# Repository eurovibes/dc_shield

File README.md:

<!-- SPDX-FileCopyrightText: 2023 Benedikt Spranger <b.spranger@linutronix.de> -
->
<!-- SPDX-License-Identifier: CERN-OHL-S-2.0 -->

# dc_shield - A IFX9201 based Arduino Uno R3 motor shield

## License rules

dc_shield is provided under the terms of the CERN-OHL-S license
version 2 as provided in the LICENSES/CERN-OHL-S-2.0 file.

Instead of adding license boilerplates to the individual files,
dc_shield uses SPDX license identifiers, which are machine parseable
and considered legaly equivalent.

The SPDX license identifier in dc_shield shall be added at the first
possible line in a file which can contain a comment. This is normally the
first line except for scripts. Scripts require the #!PATH_TO_INTERPRETER tag
in the first line; place the SPDX identifier into the second line.

The SPDX license identifier is added in form of a comment.

## Copyright and License

> Copyright Benedikt Spranger 2023.
> This source describes Open Hardware and is licensed under the CERNOHL-S v2.
> You may redistribute and modify this source and make products using it
> under the terms of the CERN-OHL-S v2 (https://ohwr.org/cern ohl s v2.txt ).
> This source is distributed WITHOUT ANY EXPRESS OR IMPLIED WARRANTY, INCLUDING
> OF MERCHANTABILITY, SATISFACTORY QUALITY AND FITNESS FOR A PARTICULAR PURPOSE.
> Please see the CERN-OHL-S v2 for applicable conditions.
> Source location: https://github.com/eurovibes/dc_shield
> As per CERN-OHL-S v2 section 4, should You produce hardware based
> on this source, You must where practicable maintain the Source Location
> visible on the external case of the dc_shield or other products you
> make using this source.

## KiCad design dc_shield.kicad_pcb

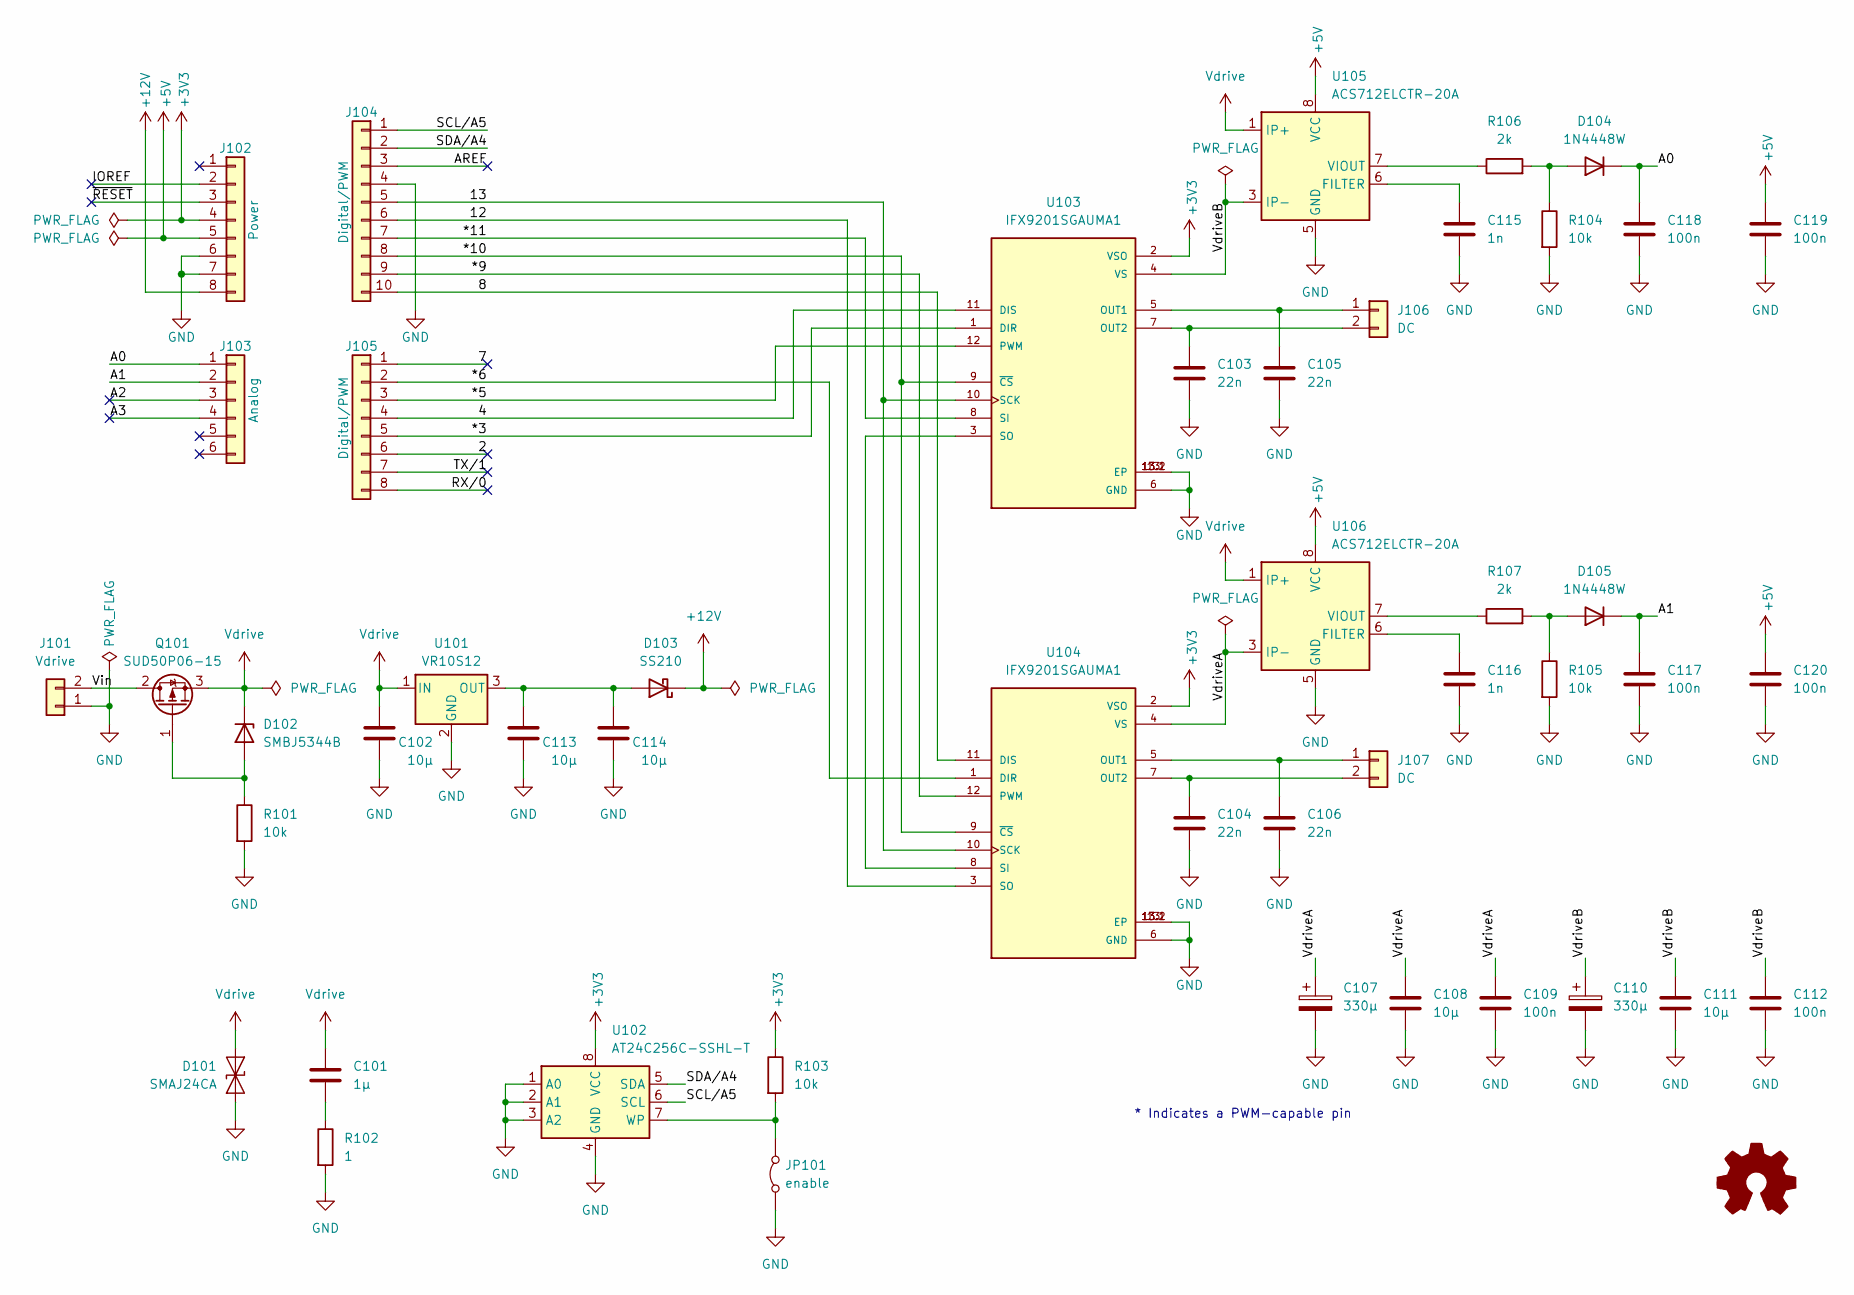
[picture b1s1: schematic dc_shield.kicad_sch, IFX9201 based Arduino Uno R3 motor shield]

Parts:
C101: 1µ; C_0603_1608Metric; mpn CL10A105KB8NNNC; LCSC# C15849
C102, C108, C111, C113, C114: 10µ; C_1206_3216Metric; mpn CL31A106KBHNNNE; LCSC# C13585
C103, C104, C105, C106: 22n; C_0603_1608Metric; mpn CL10B223KB8NNNC; LCSC# C21122
C107, C110: 330µ; CP_Elec_10x10.5; mpn VZT331M1HTR-1010; LCSC# C249985
C109, C112, C117, C118, C119, C120: 100n; C_0603_1608Metric; mpn CC0603KRX7R9BB104; LCSC# C14663
C115, C116: 1n; C_0603_1608Metric; mpn CL10B102KB8NNNC; LCSC# C1588
D101: SMAJ24CA; D_SMA; mpn SMAJ24CA; LCSC# C3001961
D102: SMBJ5344B; D_SMB; mpn SMBJ5344B; LCSC# C2903883
D103: SS210; D_SMA; mpn SS210; LCSC# C14996
D104, D105: 1N4448W; D_SOD-123; mpn 1N4448W; LCSC# C5190208
J101: Vdrive; TerminalBlock_WAGO_236-402_1x02_P5.00mm_45Degree; mpn 236-402; digikey# 2946-236-402-ND
J102: Power; PinSocket_1x08_P2.54mm_Vertical; mpn PRT-11417; digikey# 1568-1413-ND
J103: Analog; PinSocket_1x06_P2.54mm_Vertical; mpn PRT-11417; digikey# 1568-1413-ND
J104: Digital/PWM; PinSocket_1x10_P2.54mm_Vertical; mpn PRT-11417; digikey# 1568-1413-ND
J105: Digital/PWM; PinSocket_1x08_P2.54mm_Vertical; mpn PRT-11417; digikey# 1568-1413-ND
J106, J107: DC; TerminalBlock_WAGO_236-402_1x02_P5.00mm_45Degree; mpn 236-402; digikey# 2946-236-402-ND
JP101: enable; SolderJumper-2_P1.3mm_Open_Pad1.0x1.5mm; mpn N/A
Q101: SUD50P06-15; TO-252-2; mpn SUD50P06-15-GE3; LCSC# C141584
R101, R103, R104, R105: 10k; R_0402_1005Metric; mpn 0402WGF1002TCE; LCSC# C25744
R102: 1; R_1206_3216Metric; mpn 1206W4F100KT5E; LCSC# C17928
R106, R107: 2k; R_0402_1005Metric; mpn 0402WGF2001TCE; LCSC# C4109
U101: VR10S12; Converter_DCDC_RECOM_R-78E-0.5_THT; mpn VR10S12; digikey# 1470-VR10S12-ND
U102: AT24C256C-SSHL-T; SOIC-8_3.9x4.9mm_P1.27mm; mpn AT24C256C-SSHL-T; LCSC# C6482
U103, U104: IFX9201SGAUMA1; CONV_IFX9201SGAUMA1; mpn IFX9201SGAUMA1; LCSC# C112633
U105, U106: ACS712ELCTR-20A; SOIC-8_3.9x4.9mm_P1.27mm; mpn ACS712ELCTR-20A-T; LCSC# C10681

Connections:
+3V3: J102.4, R103.1, U102.8 (VCC), U103.2 (VSO), U104.2 (VSO)
+5V: C119.1, C120.1, J102.5, U105.8 (VCC), U106.8 (VCC)
+12V: D103.1 (K), J102.8
/2: J105.6
/4: J105.4, U103.11 (DIS)
/7: J105.1
/8: J104.10, U104.11 (DIS)
/12: J104.6, U104.3 (SO)
/13: J104.5, U103.10 (SCK), U104.10 (SCK)
/*3: J105.5, U103.1 (DIR)
/*5: J105.3, U103.12 (PWM)
/*6: J105.2, U104.1 (DIR)
/*9: J104.9, U104.12 (PWM)
/*10: J104.8, U103.9 (~CS), U104.9 (~CS)
/*11: J104.7, U103.8 (SI)
/A0: C118.1, D104.1 (K), J103.1
/A1: C117.1, D105.1 (K), J103.2
/A2: J103.3
/A3: J103.4
/AREF: J104.3
/IOREF: J102.2
/RX/0: J105.8
/SCL/A5: J104.1, U102.6 (SCL)
/SDA/A4: J104.2, U102.5 (SDA)
/TX/1: J105.7
/VdriveA: C107.1, C108.1, C109.1, U104.4 (VS), U106.3 (IP-), U106.4 (IP-)
/VdriveB: C110.1, C111.1, C112.1, U103.4 (VS), U105.3 (IP-), U105.4 (IP-)
/Vin: J101.2, Q101.2 (D)
/~RESET: J102.3
GND: C102.2, C103.2, C104.2, C105.2, C106.2, C107.2, C108.2, C109.2, C110.2, C111.2, C112.2, C113.2, C114.2, C115.2, C116.2, C117.2, C118.2, C119.2, C120.2, D101.1 (A1), J101.1, J102.6, J102.7, J104.4, JP101.1 (A), R101.2, R102.2, R104.2, R105.2, U101.2 (GND), U102.1 (A0), U102.2 (A1), U102.3 (A2), U102.4 (GND), U103.6 (GND), U103.13 (EP), U103.13.1 (EP), U103.13.2 (EP), U104.6 (GND), U104.13 (EP), U104.13.1 (EP), U104.13.2 (EP), U105.5 (GND), U106.5 (GND)
unnamed: C101.2, R102.1
unnamed: D102.2 (A), Q101.1 (G), R101.1
unnamed: C113.1, C114.1, D103.2 (A), U101.3 (OUT)
unnamed: D104.2 (A), R104.1, R106.2
unnamed: D105.2 (A), R105.1, R107.2
unnamed: C105.1, J106.1, U103.5 (OUT1)
unnamed: C103.1, J106.2, U103.7 (OUT2)
unnamed: C106.1, J107.1, U104.5 (OUT1)
unnamed: C104.1, J107.2, U104.7 (OUT2)
unnamed: JP101.2 (B), R103.2, U102.7 (WP)
unnamed: U103.3 (SO), U104.8 (SI)
unnamed: C115.1, U105.6 (FILTER)
unnamed: R106.1, U105.7 (VIOUT)
unnamed: C116.1, U106.6 (FILTER)
unnamed: R107.1, U106.7 (VIOUT)
Vdrive: C101.1, C102.1, D101.2 (A2), D102.1 (K), Q101.3 (S), U101.1 (IN), U105.1 (IP+), U105.2 (IP+), U106.1 (IP+), U106.2 (IP+)

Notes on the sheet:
* Indicates a PWM-capable pin

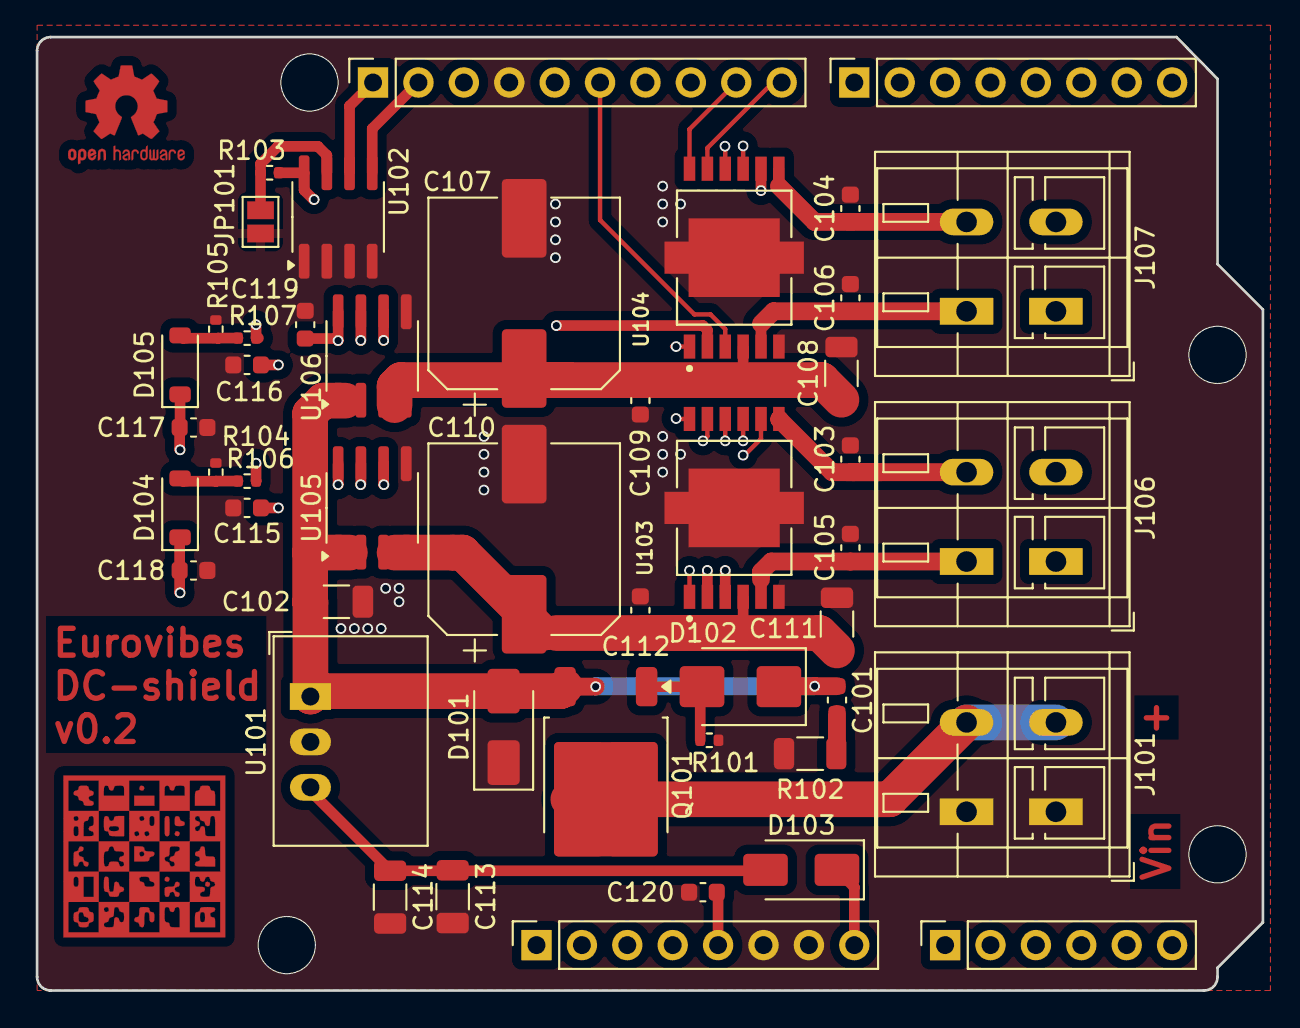
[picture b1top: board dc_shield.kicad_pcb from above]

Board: 4 copper layers, 68.6 x 53.3 mm, 51 parts (0 on the bottom side), 37 nets.

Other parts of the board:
MH1, MH2, MH3, MH4: MountingHole_3.2mm

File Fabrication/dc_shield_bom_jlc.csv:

"Comment","Designator","Footprint","LCSC Part #"
"1n","C115,C116","C_0603_1608Metric","C1588"
"22n","C103,C104,C105,C106","C_0603_1608Metric","C106222"
"100n","C109,C112,C117,C118","C_0603_1608Metric","C1591"
"1µ","C101","C_0603_1608Metric","C108343"
"10µ","C102,C108,C111,C113,C114","C_1206_3216Metric","C329928"
"330µ","C107,C110","CP_Elec_10x10.5","C5162354"
"1N4448W","D104,D105","D_SOD-123","C5190208"
"SMAJ24CA","D101","D_SMA","C3001961"
"SMBJ5344B","D102","D_SMB","C2903883"
"SS210","D103","D_SMA","C14996"
"SUD50P06-15","Q101","TO-252-2","C141584"
"1R1","R102","R_1206_3216Metric","C168518"
"2k","R106,R107","R_0402_1005Metric","C4109"
"10k","R101,R103,R104,R105","R_0402_1005Metric","C319934"
"ACS712ELCTR-20A","U105,U106","SOIC-8_3.9x4.9mm_P1.27mm","C10681"
"AT24C256C-SSHL-T","U102","SOIC-8_3.9x4.9mm_P1.27mm","C6482"
"IFX9201SGAUMA1","U103,U104","CONV_IFX9201SGAUMA1","C112633"

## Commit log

2024-06-30 Initial
2024-06-30 Add git attributes
    To avoid unnessesary changes due to internal date changes and power
    symbol enumeration.
2024-06-30 Add Logo
2024-06-30 Add build infrastructure
2024-07-01 Add project README file
2024-07-01 Add social media preview logo
2024-07-06 Initial gh-pages commit
2024-07-06 Deploying to gh-pages from @ eurovibes/dc_shield@fc2ac6369b1069db33600a8caf932f55eefd97bf 🚀
2024-07-06 Add .gitignore
2025-03-25 Deploying to gh-pages from @ eurovibes/dc_shield@60f2f6ca07b827da3a144c69103e95f7ece34d35 🚀
2025-03-25 Add current sensing
2025-03-25 Update checkout/upload action to v4
2025-03-25 Deploying to gh-pages from @ eurovibes/dc_shield@4060e44461611bf00d2d02ad8fe69f37d068c508 🚀
2025-03-25 Replace 5A current sensor by 20A variant
2025-03-25 Deploying to gh-pages from @ eurovibes/dc_shield@b4b83e717ff7e5e7c1d952959d342fe6ca09a09f 🚀
2025-03-25 Deploying to gh-pages from @ eurovibes/dc_shield@84735dd616976700509af5dc594f048494c0ab93 🚀
2025-03-25 Deploying to gh-pages from @ eurovibes/dc_shield@08116db23494f0c2567440bbd52593d50a75667d 🚀
2025-03-25 Update JLCPCB parts
2025-03-25 Deploying to gh-pages from @ eurovibes/dc_shield@61e44be7532b6fbf1e1da7e6a3e14837c423a355 🚀
2025-03-25 Add filter capacitors
2025-03-25 Deploying to gh-pages from @ eurovibes/dc_shield@f5ff49c75f3326117b95796ae41c3fb7995dba14 🚀

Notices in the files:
dc_shield.kicad_sch:
This work is licensed under the CERN-OHL-S v2
